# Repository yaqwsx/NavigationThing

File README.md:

# NavigationThing

The thing, which will safely guide you through darkness. A prop used during
[K-SCUK 2016](http://kscuk.fi.muni.cz/) night game.

# What does it do?

NavigationThing features an electronic compass and a GPS receiver, which are
used for navigation of a user through a series of waypoints. Distance to the
next waypoint is indicated via beeping, which adds a mysterious feeling. Closer
the user is, the faster the box beeps. NavigationThing is powered by 4 AA
batteries.

# How to use it?

The navigation thing is ready out of box. When you power it for the first time,
the unit beeps, goes black for 3 seconds and then the unit enters compass
calibration mode, which is indited via purple flashing. **It is necessary to
rotate the unit on a flat surface until it stops flashing.** After initial setup,
the unit starts normal operation.

During normal operation, the thing shows either electronic compass or flashes
red. Red flashing indicates missing GPS fix. The thing remembers progress in
EEPROM, so user can safely remove batteries in the middle of operation and
insert them back again. To reset the unit, simply short two pads in the left-
bottom corner of PCB during power-up. Then restart the unit.

To change waypoints, change `waypoints` array in the firmware source code. When
user enters a waypoint, an user supplied callback function is called.

# Repository Structure

The repository is organized as follow:

- `NavigationThing` contains the unit's firmware. The firmware is written in
  Arduino to keep things simple.

- `NavigationThingHwTest` contains testing firmware, which tests the PCB - LEDs
  and peripherals communication.

- `hw` contains schematics and PCBs in KiCAD

I am sorry, there are no CAD files for the box.

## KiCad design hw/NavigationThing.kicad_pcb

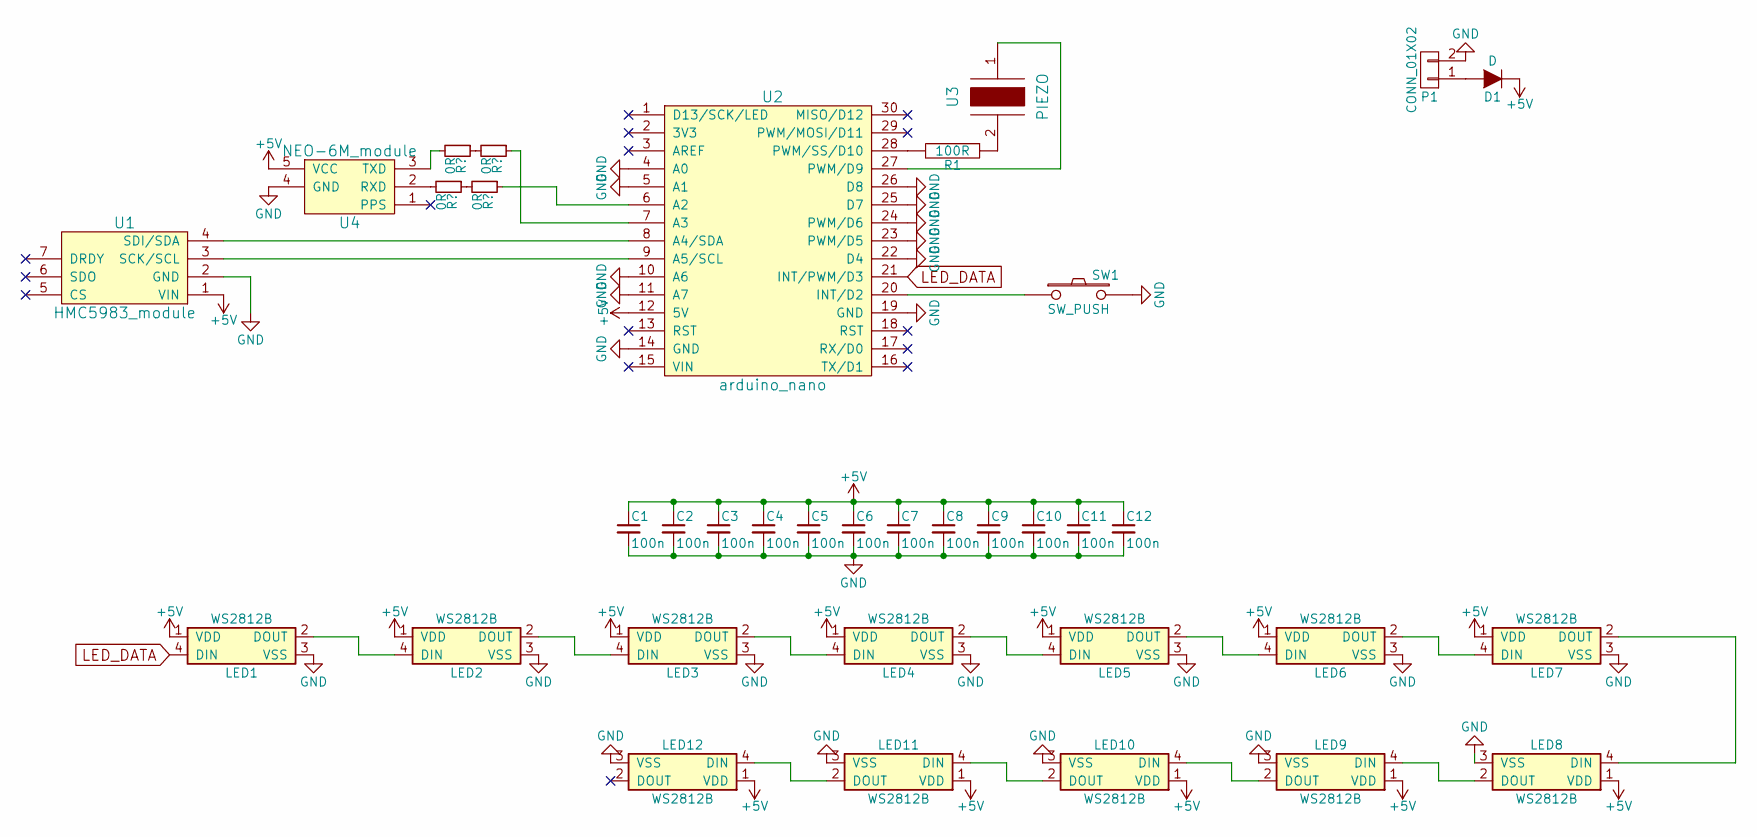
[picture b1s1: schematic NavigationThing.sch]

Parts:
C1, C2, C3, C4, C5, C6, C7, C8, C9, C10, C11, C12: 100n; C_0603
D1: D; SOD-323
LED1, LED2, LED3, LED4, LED5, LED6, LED7, LED8, LED9, LED10, LED11, LED12: WS2812B; LED_WS2812B-PLCC4
P1: CONN_01X02; Pin_Header_Straight_1x02
R1: 100R; R_0603_HandSoldering
SW1: SW_PUSH; SW_SPST_EVQPE1
U1: HMC5983_module
U2: arduino_nano
U3: PIEZO; piezo_12
U4: NEO-6M_module

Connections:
+5V: C1.1, C2.1, C3.1, C4.1, C5.1, C6.1, C7.1, C8.1, C9.1, C10.1, C11.1, C12.1, D1.1 (K), LED1.1 (VDD), LED2.1 (VDD), LED3.1 (VDD), LED4.1 (VDD), LED5.1 (VDD), LED6.1 (VDD), LED7.1 (VDD), LED8.1 (VDD), LED9.1 (VDD), LED10.1 (VDD), LED11.1 (VDD), LED12.1 (VDD), U1.1 (VIN), U2.12 (5V), U4.5 (VCC)
GND: C1.2, C2.2, C3.2, C4.2, C5.2, C6.2, C7.2, C8.2, C9.2, C10.2, C11.2, C12.2, LED1.3 (VSS), LED2.3 (VSS), LED3.3 (VSS), LED4.3 (VSS), LED5.3 (VSS), LED6.3 (VSS), LED7.3 (VSS), LED8.3 (VSS), LED9.3 (VSS), LED10.3 (VSS), LED11.3 (VSS), LED12.3 (VSS), P1.2, SW1.2, U1.2 (GND), U2.4 (A0), U2.5 (A1), U2.10 (A6), U2.11 (A7), U2.14 (GND), U2.19 (GND), U2.22 (D4), U2.23 (PWM/D5), U2.24 (PWM/D6), U2.25 (D7), U2.26 (D8), U4.4 (GND)
LED_DATA: LED1.4 (DIN), U2.21 (INT/PWM/D3)
unnamed: D1.2 (A), P1.1
unnamed: LED1.2 (DOUT), LED2.4 (DIN)
unnamed: LED2.2 (DOUT), LED3.4 (DIN)
unnamed: LED3.2 (DOUT), LED4.4 (DIN)
unnamed: LED4.2 (DOUT), LED5.4 (DIN)
unnamed: LED5.2 (DOUT), LED6.4 (DIN)
unnamed: LED6.2 (DOUT), LED7.4 (DIN)
unnamed: LED7.2 (DOUT), LED8.4 (DIN)
unnamed: LED8.2 (DOUT), LED9.4 (DIN)
unnamed: LED10.2 (DOUT), LED11.4 (DIN)
unnamed: LED9.2 (DOUT), LED10.4 (DIN)
unnamed: LED11.2 (DOUT), LED12.4 (DIN)
unnamed: R1.1, U3.2
unnamed: R1.2, U2.28 (PWM/SS/D10)
unnamed 18: U4.2 (RXD); also elsewhere on the board
unnamed 20: U4.3 (TXD); also elsewhere on the board
unnamed 21: U2.6 (A2); also elsewhere on the board
unnamed 22: U2.7 (A3); also elsewhere on the board
unnamed: SW1.1, U2.20 (INT/D2)
unnamed: U1.3 (SCK/SCL), U2.9 (A5/SCL)
unnamed: U1.4 (SDI/SDA), U2.8 (A4/SDA)
unnamed: U2.27 (PWM/D9), U3.1

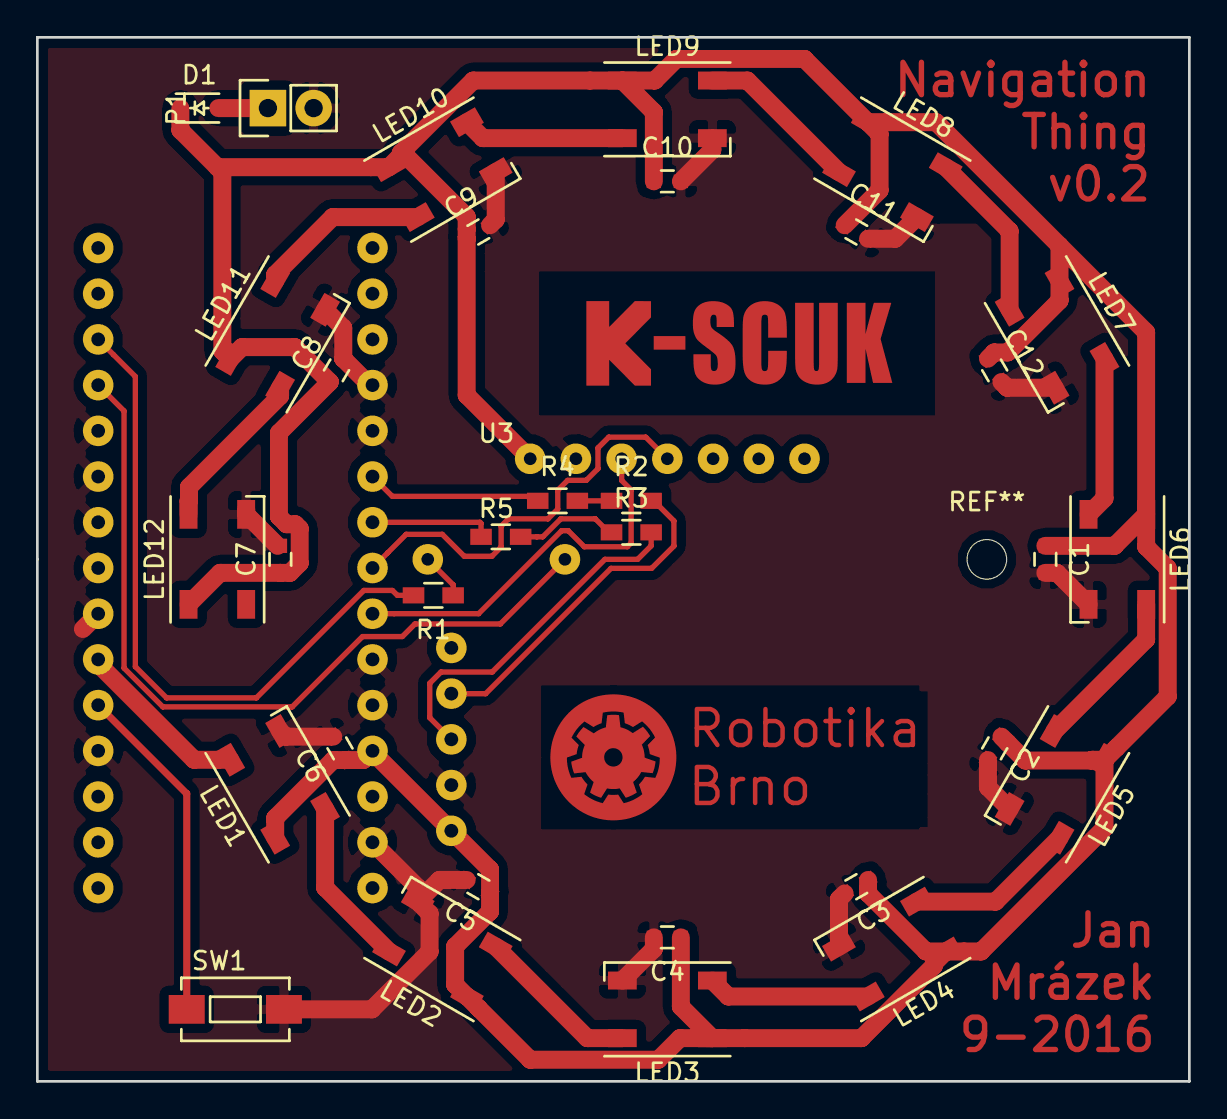
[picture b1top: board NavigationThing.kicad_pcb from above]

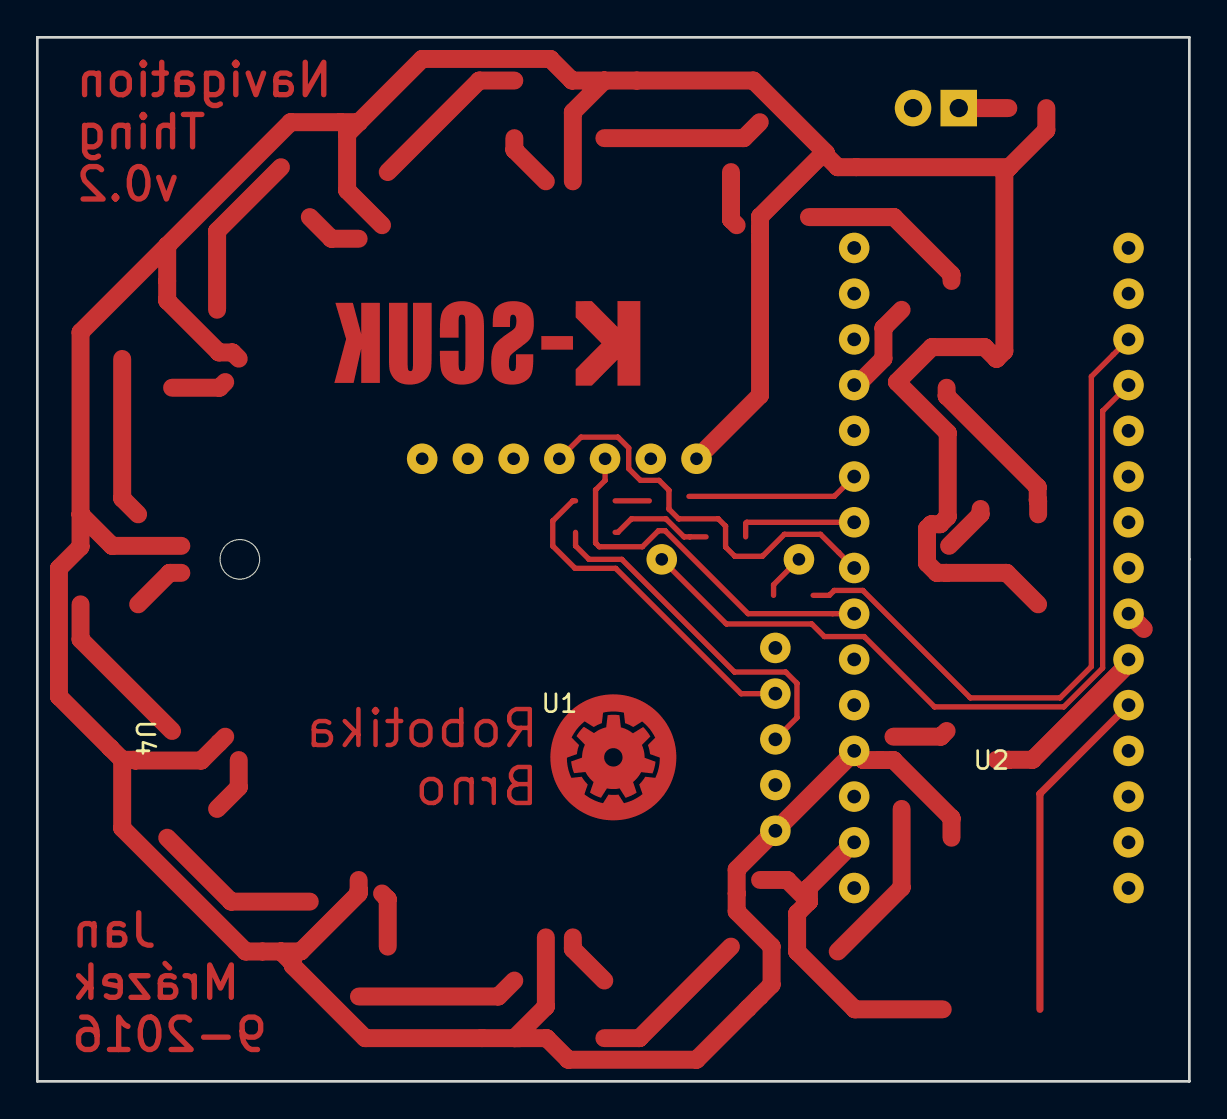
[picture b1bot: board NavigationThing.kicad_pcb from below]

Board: 2 copper layers, 64.0 x 58.0 mm, 38 parts (3 on the bottom side), 27 nets.

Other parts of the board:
R2, R3, R4, R5: 0R; R_0603_HandSoldering
svg2mod: G***; robotarna_cu_7mm
svg2mod#2: G***; kscuk_cu_17mm

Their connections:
unnamed: R2.1, R4.2
unnamed 18: R2.2; also elsewhere on the board
unnamed: R3.1, R5.2
unnamed 20: R3.2; also elsewhere on the board
unnamed 21: R4.1; also elsewhere on the board
unnamed 22: R5.1; also elsewhere on the board

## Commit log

2016-09-05 Board version 0.1
2016-09-05 New board version
    - change GPS pins, as the original ones were purely ADC
    - move piezo a little bit to make space for GPS antenna
    - add hole for GPS antenna
    - change signature to text instead of logo (which does not render in SVG)
2016-09-16 Add HW test firmware
2016-09-16 Add firmware used during the game
2016-09-16 Small board adjustements
2016-09-16 Remove dead code.
2016-09-16 Add game guide
2016-09-16 Add backlight breakout
2016-09-16 Add readme
